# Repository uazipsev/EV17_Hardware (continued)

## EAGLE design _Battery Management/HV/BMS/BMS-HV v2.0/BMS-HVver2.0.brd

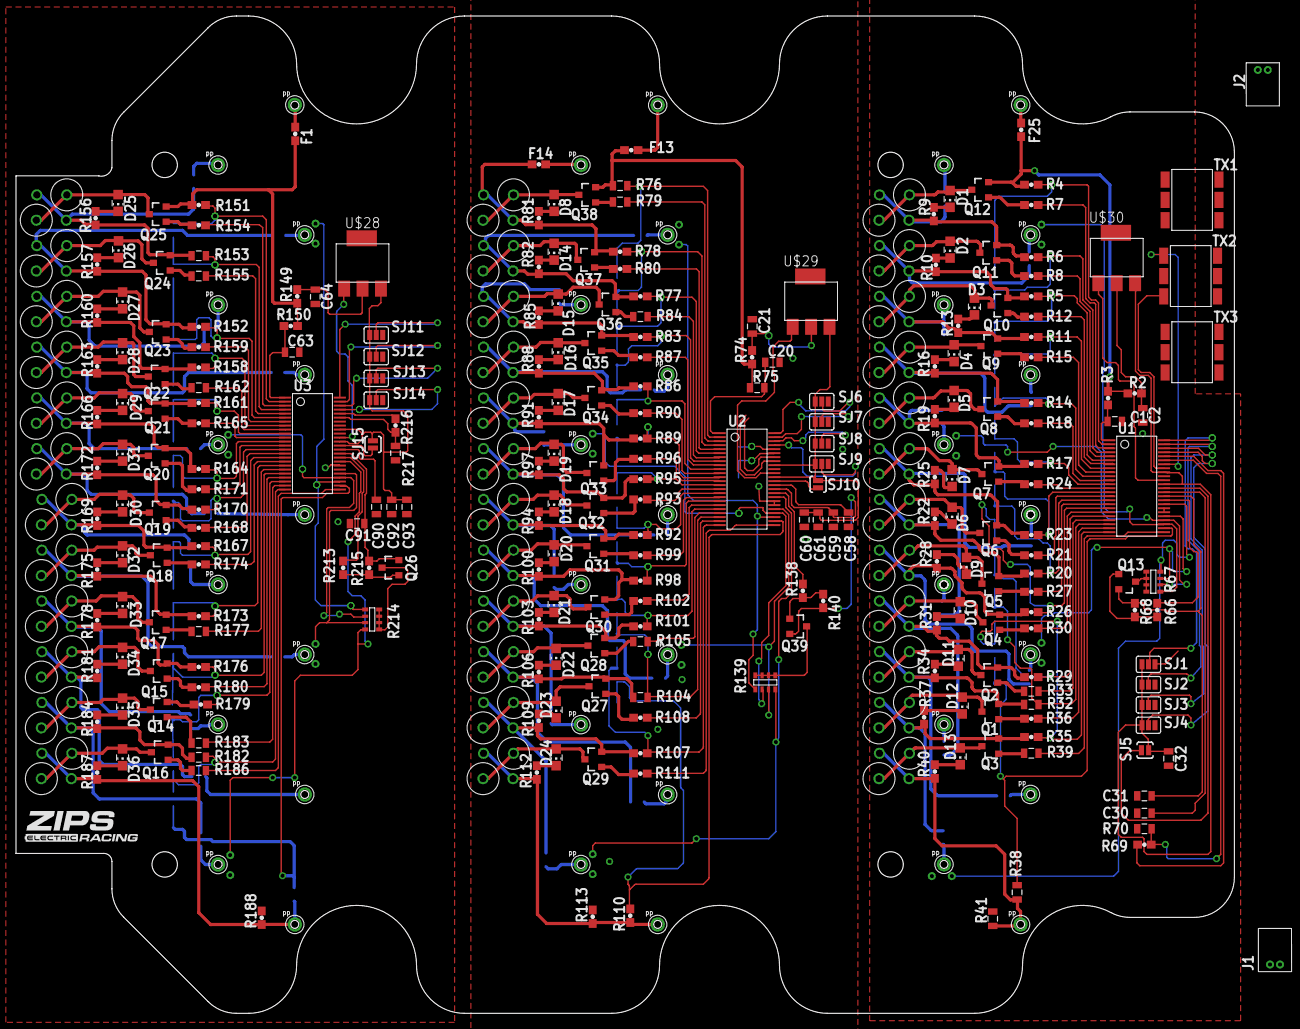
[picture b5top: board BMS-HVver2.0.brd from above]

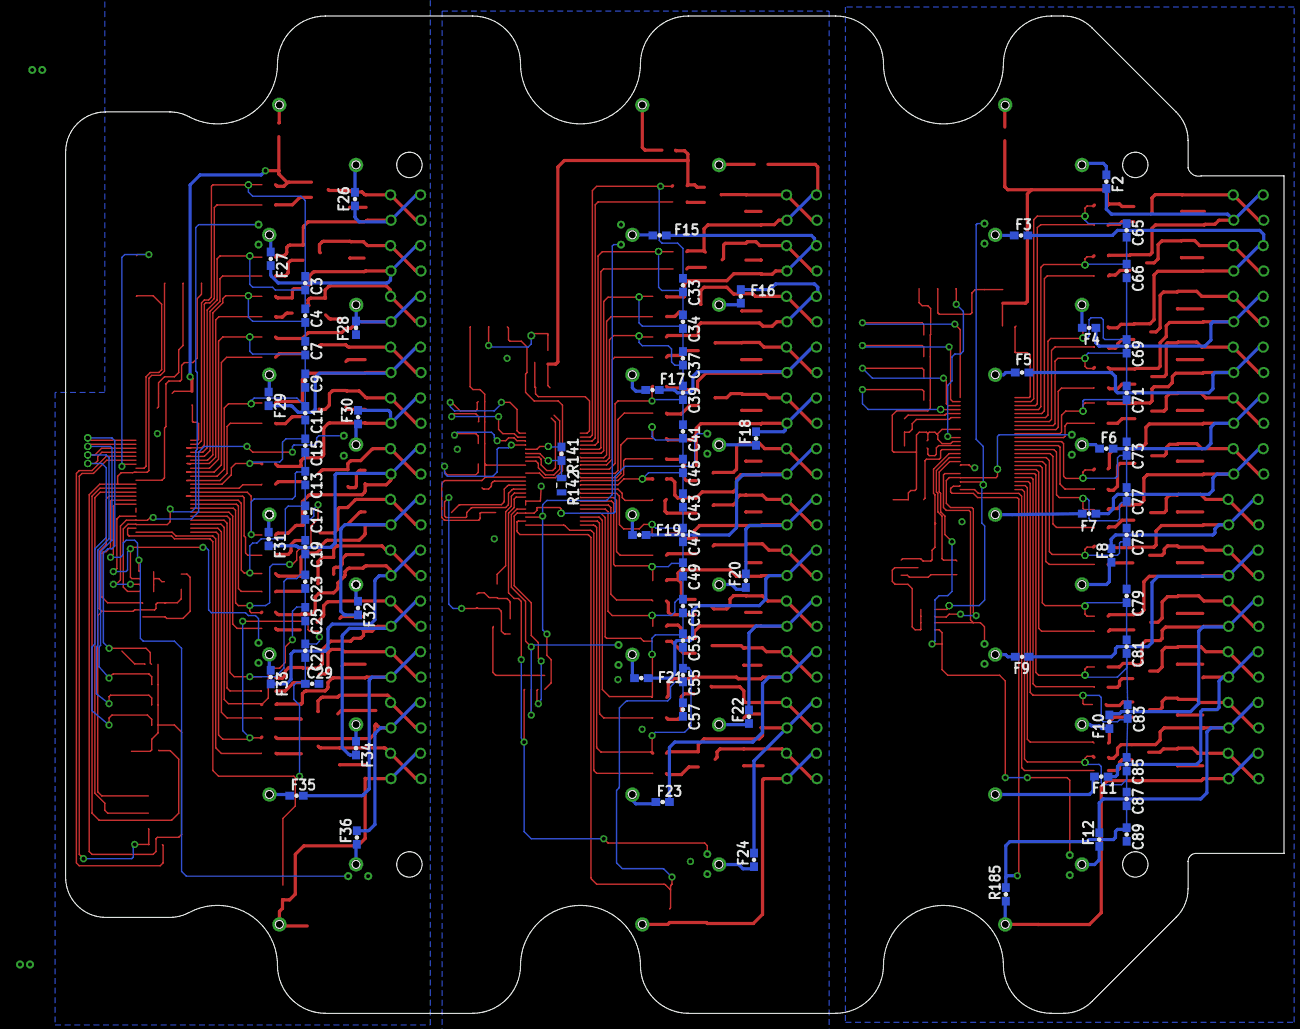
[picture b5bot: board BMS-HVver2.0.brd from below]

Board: 2 copper layers, 152.4 x 124.8 mm, 452 parts (74 on the bottom side), 329 nets.

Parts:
C1, C2, C20, C21, C63, C64: 0.1UF; 0805
C3, C4, C7, C9, C11, C13, C15, C17, C19, C23, C25, C27, C29, C33, C34, C37, C39, C41, C43, C45, C47, C49, C51, C53, C55, C57, C65, C66, C69, C71, C73, C75, C77, C79, C81, C83, C85, C87, C89: 10NF; 0603
C30, C31, C32, C58, C59, C60, C61, C90, C91, C92, C93: 1UF; 0805
D1, D2, D3, D4, D5, D6, D7, D8, D9, D10, D11, D12, D13, D14, D15, D16, D17, D18, D19, D20, D21, D22, D23, D24, D25, D26, D27, D28, D29, D30, D31, D32, D33, D34, D35, D36: LED_RED; CHIP_LED0805
F1, F2, F3, F4, F5, F6, F7, F8, F9, F10, F11, F12, F13, F14, F15, F16, F17, F18, F19, F20, F21, F22, F23, F24, F25, F26, F27, F28, F29, F30, F31, F32, F33, F34, F35, F36: FUSE_750MA_63V_0603; 0603
J1, J2: M2_DF13-2P; DF13-2P
Q1, Q2, Q3, Q4, Q5, Q6, Q7, Q8, Q9, Q10, Q11, Q12, Q13, Q14, Q15, Q16, Q17, Q18, Q19, Q20, Q21, Q22, Q23, Q24, Q25, Q26, Q27, Q28, Q29, Q30, Q31, Q32, Q33, Q34, Q35, Q36, Q37, Q38, Q39: BSS308PE; SOT23
R2, R3, R4, R5, R6, R11, R14, R17, R20, R23, R26, R29, R35, R74, R77, R78, R83, R86, R89, R92, R95, R98, R101, R107, R110, R149, R150, R151, R152, R158, R161, R164, R167, R170, R173, R176, R179, R185: 100; 0603
R7, R8, R12, R15, R18, R21, R24, R27, R30, R36, R80, R87, R90, R93, R96, R99, R102, R108, R111, R154, R159, R165, R168, R171, R174, R180: 3.3K; 0603
R9, R10, R13, R16, R19, R22, R25, R28, R31, R34, R37, R40, R81, R82, R85, R88, R91, R94, R97, R100, R103, R106, R109, R112, R156, R157, R160, R163, R166, R169, R172, R175, R178, R181, R184, R187: 475; 0603
R32, R38, R75, R76, R104, R153, R182: 100; 0805
R33, R39, R79, R84, R105, R155, R162, R177, R183, R186: 3.3K; 0805
R41: 0; 0805
R42, R43, R44, R45, R46, R47, R48, R49, R50, R51, R52, R53, R54, R55, R56, R57, R58, R59, R60, R61, R62, R63, R64, R65, R114, R115, R116, R117, R118, R119, R120, R121, R122, R123, R124, R125, R126, R127, R128, R129, R130, R131, R132, R133, R134, R135, R136, R137, R189, R190, R191, R192, R193, R194, R195, R196, R197, R198, R199, R200, R201, R202, R203, R204, R205, R206, R207, R208, R209, R210, R211, R212: 16; RR02J16RTB
R66, R138, R213: 1K; 0603
R67, R139, R214: 10K; MNR14
R68, R140, R215: 100K; 0603
R69, R141, R216: 1.2K; 0603
R70, R142, R217: 787; 0805
R71, R72, R73, R143, R144, R145, R146, R147, R218, R219, R220, R221: 10K-NTC; NTC-NXRT15XH103FA5B
R113, R188: 0; 0603
SJ1, SJ2, SJ3, SJ4, SJ6, SJ7, SJ8, SJ9, SJ11, SJ12, SJ13, SJ14: PAD-JUMPER-3-NO_YES_SILK
SJ5, SJ10, SJ15: PAD-JUMPER-2-NO_YES_SILK
TX1, TX2, TX3: PE-68386NLT
U1, U2, U3: LTC6804-2; SSOP-48
U$1, U$2, U$3, U$4, U$5, U$6, U$7, U$8, U$9, U$10, U$11, U$12, U$13, U$14, U$15, U$16, U$17, U$18, U$19, U$20, U$21, U$22, U$23, U$24, U$25, U$26, U$40, U$41, U$42, U$43, U$44, U$45, U$46, U$47, U$48, U$49, U$50, U$51, U$52: POGOPIN
U$27: LOGO16-2-L; 2016-2-LOGO-L
U$28, U$29, U$30: NSV1C201MZ4T1G; SOT223

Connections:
A0: SJ9.2, U2.45
A1: SJ8.2, U2.46
A2: SJ7.2, U2.47
A3: SJ6.2, U2.48
A4: SJ4.2, U1.45
A5: SJ3.2, U1.46
A6: SJ2.2, U1.47
A7: SJ1.2, U1.48
A8: SJ14.2, U3.45
A9: SJ13.2, U3.46
A10: SJ12.2, U3.47
A11: SJ11.2, U3.48
C0: C55.2, C57.1, R110.2, U2.26
C1: C53.2, C55.1, R107.2, U2.24
C2: C51.2, C53.1, R104.2, U2.22
C3: C49.2, C51.1, R101.2, U2.20
C4: C47.2, C49.1, R98.2, U2.18
C5: C43.2, C47.1, R92.2, U2.16
C6: C43.1, C45.2, R95.2, U2.14
C7: C41.2, C45.1, R89.2, U2.12
C8: C39.2, C41.1, R86.2, U2.10
C9: C37.2, C39.1, R83.2, U2.8
C10: C34.2, C37.1, R77.2, U2.6
C11: C33.2, C34.1, R78.2, U2.4
C12: C33.1, R76.2, U2.2
C13: C3.1, R4.2, U1.2
C14: C3.2, C4.1, R6.2, U1.4
C15: C7.2, C9.1, R11.2, U1.8
C16: C11.2, C15.1, R17.2, U1.12
C17: C13.1, C15.2, R23.2, U1.14
C18: C13.2, C17.1, R20.2, U1.16
C19: C19.2, C23.1, R29.2, U1.20
C20: C23.2, C25.1, R32.2, U1.22
C21: C25.2, C27.1, R35.2, U1.24
C22: C4.2, C7.1, R5.2, U1.6
C23: C27.2, C29.1, R38.2, U1.26
C24: C17.2, C19.1, R26.2, U1.18
C25: C9.2, C11.1, R14.2, U1.10
C26: C65.1, R151.2, U3.2
C27: C65.2, C66.1, R153.2, U3.4
C28: C69.2, C71.1, R158.2, U3.8
C29: C73.2, C77.1, R164.2, U3.12
C30: C75.1, C77.2, R170.2, U3.14
C31: C75.2, C79.1, R167.2, U3.16
C32: C81.2, C83.1, R176.2, U3.20
C33: C83.2, C85.1, R179.2, U3.22
C34: C85.2, C87.1, R182.2, U3.24
C35: C66.2, C69.1, R152.2, U3.6
C36: C87.2, C89.1, R185.2, U3.26
C37: C79.2, C81.1, R173.2, U3.18
C38: C71.2, C73.1, R161.2, U3.10
DRIVE: U2.38, U$29.P$1
DRIVE1: U1.38, U$30.P$1
DRIVE2: U3.38, U$28.P$1
GND: C63.2, C64.2, C89.2, C90.2, C91.2, C92.2, C93.2, R188.2, R217.1, R218.P$1, R219.P$1, R220.P$1, R221.P$1, SJ11.3, SJ12.3, SJ13.3, SJ14.3, U3.30, U3.31
GNDA: C20.2, C21.2, C57.2, C58.2, C59.2, C60.2, C61.2, R113.2, R142.1, R143.P$1, R144.P$1, R145.P$1, R146.P$1, SJ6.3, SJ7.3, SJ8.3, SJ9.3, U2.30, U2.31
GNDI: C1.2, C2.2, C29.2, C30.2, C31.2, C32.2, R41.2, R70.1, R71.P$1, R72.P$1, R73.P$1, R147.P$1, SJ1.3, SJ2.3, SJ3.3, SJ4.3, U1.30, U1.31
GPIO1: R139.1, R143.P$2, U2.27
GPIO2: R139.2, R144.P$2, U2.28
GPIO3: R139.3, R145.P$2, U2.29
GPIO4: R139.4, R146.P$2, U2.32
GPIO5: R138.2, U2.33
GPIO6: R67.2, R72.P$2, U1.28
GPIO7: R67.1, R71.P$2, U1.27
GPIO8: R67.4, R147.P$2, U1.32
GPIO9: R67.3, R73.P$2, U1.29
GPIO10: R66.2, U1.33
GPIO11: R214.2, R219.P$2, U3.28
GPIO12: R214.1, R218.P$2, U3.27
GPIO13: R214.4, R221.P$2, U3.32
GPIO14: R214.3, R220.P$2, U3.29
GPIO15: R213.2, U3.33
IBIAS: R141.2, U2.44
IBIAS1: R69.2, U1.44
IBIAS2: R216.2, U3.44
ICMP: R141.1, R142.2, U2.43
ICMP1: R69.1, R70.2, U1.43
ICMP2: R216.1, R217.2, U3.43
IMA: TX1.3, U2.41
IMA1: TX2.3, U1.41
IMA2: TX3.3, U3.41
IPA: TX1.1, U2.42
IPA1: TX2.1, U1.42
IPA2: TX3.1, U3.42
unnamed: Q12.1, R7.1
unnamed: D1.A, Q12.3, R64.P$2, R65.P$2
unnamed: D1.C, R9.2
unnamed: F26.2, Q11.2, R6.1, R9.1, R64.P$1, R65.P$1
unnamed: Q11.1, R8.1
unnamed: D2.A, Q11.3, R62.P$2, R63.P$2
unnamed: D2.C, R10.2
unnamed: F27.2, Q10.2, R5.1, R10.1, R62.P$1, R63.P$1
unnamed: Q10.1, R12.1
unnamed: D3.A, Q10.3, R60.P$2, R61.P$2
unnamed: D3.C, R13.2
unnamed: F28.2, Q9.2, R11.1, R13.1, R60.P$1, R61.P$1
unnamed: Q9.1, R15.1
unnamed: D4.A, Q9.3, R58.P$2, R59.P$2
unnamed: D4.C, R16.2
unnamed: F29.2, Q8.2, R14.1, R16.1, R58.P$1, R59.P$1
unnamed: Q8.1, R18.1
unnamed: D5.A, Q8.3, R56.P$2, R57.P$2
unnamed: D5.C, R19.2
unnamed: Q6.1, R21.1
unnamed: D6.A, Q6.3, R52.P$2, R53.P$2
unnamed: D6.C, R22.2
unnamed: F30.2, Q7.2, R17.1, R19.1, R56.P$1, R57.P$1
unnamed: Q7.1, R24.1
unnamed: D7.A, Q7.3, R54.P$2, R55.P$2
unnamed: D7.C, R25.2
unnamed: F31.2, Q6.2, R23.1, R25.1, R54.P$1, R55.P$1
unnamed: F32.2, Q5.2, R20.1, R22.1, R52.P$1, R53.P$1
unnamed: Q5.1, R27.1
unnamed: D9.A, Q5.3, R50.P$2, R51.P$2
unnamed: D9.C, R28.2
unnamed: F33.2, Q4.2, R26.1, R28.1, R50.P$1, R51.P$1
unnamed: Q4.1, R30.1
unnamed: D10.A, Q4.3, R48.P$2, R49.P$2
unnamed: D10.C, R31.2
unnamed: F34.2, Q2.2, R29.1, R31.1, R48.P$1, R49.P$1
unnamed: Q2.1, R33.1
unnamed: D11.A, Q2.3, R46.P$2, R47.P$2
unnamed: D11.C, R34.2
unnamed: F35.2, Q1.2, R32.1, R34.1, R46.P$1, R47.P$1
unnamed: Q1.1, R36.1
unnamed: D12.A, Q1.3, R44.P$2, R45.P$2
unnamed: D12.C, R37.2
unnamed: Q3.1, R39.1
unnamed: D13.C, R40.2
unnamed: F25.2, Q12.2, R2.1, R3.1, R4.1
unnamed: D13.A, Q3.3, R42.P$2, R43.P$2
unnamed: R38.1, R40.1, R41.1, R42.P$1, R43.P$1, U$1.1
unnamed: F36.2, Q3.2, R35.1, R37.1, R44.P$1, R45.P$1
unnamed: C2.1, R2.2, U$30.P$2
unnamed: Q13.3, R67.5, R67.6, R67.7, R67.8
unnamed: Q13.1, R66.1, R68.1
unnamed: Q25.1, R154.1
unnamed: D25.A, Q25.3, R211.P$2, R212.P$2
unnamed: D25.C, R156.2
unnamed: F2.2, Q24.2, R153.1, R156.1, R211.P$1, R212.P$1
unnamed: Q24.1, R155.1
unnamed: D26.A, Q24.3, R209.P$2, R210.P$2
unnamed: D26.C, R157.2
unnamed: F3.2, Q23.2, R152.1, R157.1, R209.P$1, R210.P$1
unnamed: Q23.1, R159.1
unnamed: D27.A, Q23.3, R207.P$2, R208.P$2
unnamed: D27.C, R160.2
unnamed: F4.2, Q22.2, R158.1, R160.1, R207.P$1, R208.P$1
unnamed: Q22.1, R162.1
unnamed: D28.A, Q22.3, R205.P$2, R206.P$2
unnamed: D28.C, R163.2
unnamed: F5.2, Q21.2, R161.1, R163.1, R205.P$1, R206.P$1
unnamed: Q21.1, R165.1
unnamed: D29.A, Q21.3, R203.P$2, R204.P$2
unnamed: D29.C, R166.2
unnamed: Q19.1, R168.1
unnamed: D30.A, Q19.3, R199.P$2, R200.P$2
unnamed: D30.C, R169.2
unnamed: F6.2, Q20.2, R164.1, R166.1, R203.P$1, R204.P$1
unnamed: Q20.1, R171.1
unnamed: D31.A, Q20.3, R201.P$2, R202.P$2
unnamed: D31.C, R172.2
unnamed: F7.2, Q19.2, R170.1, R172.1, R201.P$1, R202.P$1
unnamed: F8.2, Q18.2, R167.1, R169.1, R199.P$1, R200.P$1
unnamed: Q18.1, R174.1
unnamed: D32.A, Q18.3, R197.P$2, R198.P$2
unnamed: D32.C, R175.2
unnamed: F9.2, Q17.2, R173.1, R175.1, R197.P$1, R198.P$1
unnamed: Q17.1, R177.1
unnamed: D33.A, Q17.3, R195.P$2, R196.P$2
unnamed: D33.C, R178.2
unnamed: F10.2, Q15.2, R176.1, R178.1, R195.P$1, R196.P$1
unnamed: Q15.1, R180.1
unnamed: D34.A, Q15.3, R193.P$2, R194.P$2
unnamed: D34.C, R181.2
unnamed: F11.2, Q14.2, R179.1, R181.1, R193.P$1, R194.P$1
unnamed: Q14.1, R183.1
unnamed: D35.A, Q14.3, R191.P$2, R192.P$2
unnamed: D35.C, R184.2
unnamed: Q16.1, R186.1
unnamed: D36.C, R187.2
unnamed: F1.2, Q25.2, R149.1, R150.1, R151.1
unnamed: D36.A, Q16.3, R189.P$2, R190.P$2
unnamed: Q38.1, R79.1
unnamed: D8.A, Q38.3, R136.P$2, R137.P$2
unnamed: D8.C, R81.2
unnamed: R185.1, R187.1, R188.1, R189.P$1, R190.P$1, U$14.1
unnamed: F12.2, Q16.2, R182.1, R184.1, R191.P$1, R192.P$1
unnamed: C64.1, R149.2, U$28.P$2
unnamed: F14.2, Q37.2, R78.1, R81.1, R136.P$1, R137.P$1
unnamed: Q37.1, R80.1
unnamed: D14.A, Q37.3, R134.P$2, R135.P$2
unnamed: D14.C, R82.2
unnamed: F15.2, Q36.2, R77.1, R82.1, R134.P$1, R135.P$1
unnamed: Q26.3, R214.5, R214.6, R214.7, R214.8
unnamed: Q36.1, R84.1
unnamed: D15.A, Q36.3, R132.P$2, R133.P$2
unnamed: D15.C, R85.2
unnamed: F16.2, Q35.2, R83.1, R85.1, R132.P$1, R133.P$1
unnamed: Q26.1, R213.1, R215.1
unnamed: Q35.1, R87.1
unnamed: D16.A, Q35.3, R130.P$2, R131.P$2
unnamed: D16.C, R88.2
unnamed: F17.2, Q34.2, R86.1, R88.1, R130.P$1, R131.P$1
unnamed: J1.2, J2.1, TX1.6, TX2.6, TX3.6
unnamed: Q34.1, R90.1
unnamed: D17.A, Q34.3, R128.P$2, R129.P$2
unnamed: D17.C, R91.2
unnamed: J1.1, J2.2, TX1.4, TX2.4, TX3.4
unnamed: Q32.1, R93.1
unnamed: D18.A, Q32.3, R124.P$2, R125.P$2
unnamed: D18.C, R94.2
unnamed: C90.1, U3.35
unnamed: F18.2, Q33.2, R89.1, R91.1, R128.P$1, R129.P$1
unnamed: C30.1, U1.35
unnamed: Q33.1, R96.1
unnamed: D19.A, Q33.3, R126.P$2, R127.P$2
unnamed: D19.C, R97.2
unnamed: F19.2, Q32.2, R95.1, R97.1, R126.P$1, R127.P$1
unnamed: F20.2, Q31.2, R92.1, R94.1, R124.P$1, R125.P$1
unnamed: Q31.1, R99.1
unnamed: D20.A, Q31.3, R122.P$2, R123.P$2
unnamed: D20.C, R100.2
unnamed: F21.2, Q30.2, R98.1, R100.1, R122.P$1, R123.P$1
unnamed: Q30.1, R102.1
unnamed: D21.A, Q30.3, R120.P$2, R121.P$2
unnamed: D21.C, R103.2
unnamed: F22.2, Q28.2, R101.1, R103.1, R120.P$1, R121.P$1
unnamed: Q28.1, R105.1
unnamed: D22.A, Q28.3, R118.P$2, R119.P$2
unnamed: D22.C, R106.2
unnamed: F23.2, Q27.2, R104.1, R106.1, R118.P$1, R119.P$1
unnamed: Q27.1, R108.1
unnamed: D23.A, Q27.3, R116.P$2, R117.P$2
unnamed: D23.C, R109.2
unnamed: Q29.1, R111.1
unnamed: D24.C, R112.2
unnamed: F13.2, Q38.2, R74.1, R75.1, R76.1
unnamed: D24.A, Q29.3, R114.P$2, R115.P$2
unnamed: R110.1, R112.1, R113.1, R114.P$1, R115.P$1, U$40.1
unnamed: F24.2, Q29.2, R107.1, R109.1, R116.P$1, R117.P$1
unnamed: C21.1, R74.2, U$29.P$2
unnamed: Q39.3, R139.5, R139.6, R139.7, R139.8
unnamed: Q39.1, R138.1, R140.1
unnamed: F12.1, U$15.1
unnamed: F11.1, U$16.1
unnamed: F10.1, U$17.1
unnamed: F9.1, U$18.1
unnamed: F8.1, U$19.1
unnamed: F7.1, U$20.1
unnamed: F6.1, U$21.1
unnamed: F5.1, U$22.1
unnamed: F4.1, U$23.1
unnamed: F3.1, U$24.1
unnamed: F2.1, U$25.1
unnamed: F1.1, U$26.1
unnamed: F24.1, U$41.1
unnamed: F23.1, U$42.1
unnamed: F22.1, U$43.1
unnamed: F21.1, U$44.1
unnamed: F20.1, U$45.1
unnamed: F19.1, U$46.1
unnamed: F18.1, U$47.1
unnamed: F17.1, U$48.1
unnamed: F16.1, U$49.1
unnamed: F15.1, U$50.1
unnamed: F14.1, U$51.1
unnamed: F13.1, U$52.1
unnamed: F36.1, U$2.1
unnamed: F35.1, U$3.1
unnamed: F34.1, U$4.1
unnamed: F33.1, U$5.1
unnamed: F32.1, U$6.1
unnamed: F31.1, U$7.1
unnamed: F30.1, U$8.1
unnamed: F29.1, U$9.1
unnamed: F28.1, U$10.1
unnamed: F27.1, U$11.1
unnamed: F26.1, U$12.1
unnamed: F25.1, U$13.1
S1: R111.2, U2.25
S2: R108.2, U2.23
S3: R105.2, U2.21
S4: R102.2, U2.19
S5: R99.2, U2.17
S6: R93.2, U2.15
S7: R96.2, U2.13
S8: R90.2, U2.11
S9: R87.2, U2.9
S10: R84.2, U2.7
S11: R80.2, U2.5
S12: R79.2, U2.3
S13: R7.2, U1.3
S14: R8.2, U1.5
S15: R12.2, U1.7
S16: R15.2, U1.9
S17: R18.2, U1.11
S18: R21.2, U1.15
S19: R24.2, U1.13
S20: R27.2, U1.17
S21: R30.2, U1.19
S22: R33.2, U1.21
S23: R36.2, U1.23
S24: R39.2, U1.25
S25: R154.2, U3.3
S26: R155.2, U3.5
S27: R159.2, U3.7
S28: R162.2, U3.9
S29: R165.2, U3.11
S30: R168.2, U3.15
S31: R171.2, U3.13
S32: R174.2, U3.17
S33: R177.2, U3.19
S34: R180.2, U3.21
S35: R183.2, U3.23
S36: R186.2, U3.25
SWTEN: SJ10.1, U2.36
SWTEN1: SJ5.1, U1.36
SWTEN2: SJ15.1, U3.36
V+: C20.1, R75.2, U2.1
V+1: C1.1, R3.2, U1.1
V+2: C63.1, R150.2, U3.1
VREF1: C58.1, U2.35
VREF2: C59.1, Q39.2, R140.2, U2.34
VREF4: C31.1, Q13.2, R68.2, U1.34
VREF6: C91.1, Q26.2, R215.2, U3.34
VREG: C60.1, C61.1, SJ6.1, SJ7.1, SJ8.1, SJ9.1, SJ10.2, U2.37, U2.40, U$29.P$3
VREG1: C32.1, SJ1.1, SJ2.1, SJ3.1, SJ4.1, SJ5.2, U1.37, U1.40, U$30.P$3
VREG2: C92.1, C93.1, SJ11.1, SJ12.1, SJ13.1, SJ14.1, SJ15.2, U3.37, U3.40, U$28.P$3

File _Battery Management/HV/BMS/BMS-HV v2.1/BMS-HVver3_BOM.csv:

Qty-1,Part References,Value,Package,Mfg Part Num,Mfg Name,VID,Vendor Part Num,Description,Pkg Code,XREF
3,"SJ5, SJ10, SJ15",,PAD-JUMPER-2-NO_YES_SILK,***PART# '*' NOT FOUND***,*,*,*,*,*,*
12,"SJ1, SJ2, SJ3, SJ4, SJ6, SJ7, SJ8, SJ9, SJ11, SJ12, SJ13, SJ14",,PAD-JUMPER-3-NO_YES_SILK,***PART# '*' NOT FOUND***,*,*,*,*,*,*
36,"R1, R42, R43, R44, R45, R46, R47, R48, R49, R50, R51, R52, R53, R114, R115, R116, R117, R118, R119, R120, R121, R122, R123, R124, R125, R148, R189, R190, R191, R192, R193, R194, R195, R196, R197, R198",,R2512,***PART# '*' NOT FOUND***,*,*,*,*,*,*
2,"R113, R188",0,0603,CRCW06030000Z0EA,Vishay Dale,DK,541-0.0GCT-ND,RES SMD 0.0OHM JUMPER 1/10W 0603,0603 (1608 Metric),REF167
1,"R41",0,0805,RC0805JR-070RL,Yageo,DK,311-0.0ARCT-ND,RES SMD 0.0 OHM JUMPER 1/8W 0805,0805 (2012 Metric),REF310
6,"C1, C2, C20, C21, C63, C64",0.1UF,0805,CL21B104KCC5PNC,Samsung Electro-Mechanics America, Inc.,DK,1276-2447-1-ND,CAP CER 0.1UF 100V X7R 0805,0805 (2012 Metric),REF253
3,"R69, R141, R216",1.2K,0603,RC0603JR-071K2L,Yageo,DK,311-1.2KGRCT-ND,RES SMD 1.2K OHM 5% 1/10W 0603,0603 (1608 Metric),REF88
3,"R66, R138, R213",1K,0603,RC0603JR-071KL,Yageo,DK,311-1.0KGRCT-ND,RES SMD 1K OHM 5% 1/10W 0603,0603 (1608 Metric),REF84
12,"C5, C30, C31, C32, C58, C59, C60, C61, C90, C91, C92, C93",1UF,0805,UMK212F105ZG-T,Taiyo Yuden,DK,587-1308-1-ND,CAP CER 1UF 50V Y5V 0805,0805 (2012 Metric),REF17
3,"R54, R55, R56",1k,0603,RC0603JR-071KL,Yageo,DK,311-1.0KGRCT-ND,RES SMD 1K OHM 5% 1/10W 0603,0603 (1608 Metric),REF84
26,"R7, R8, R12, R15, R18, R21, R24, R27, R30, R36, R80, R87, R90, R93, R96, R99, R102, R108, R111, R154, R159, R165, R168, R171, R174, R180",3.3K,0603,RC0603JR-073K3L,Yageo,DK,311-3.3KGRCT-ND,RES SMD 3.3K OHM 5% 1/10W 0603,0603 (1608 Metric),REF89
10,"R33, R39, R79, R84, R105, R155, R162, R177, R183, R186",3.3K,0805,RC0805FR-073K3L,Yageo,DK,311-3.30KCRCT-ND,RES SMD 3.3K OHM 1% 1/8W 0805,0805 (2012 Metric),REF128
3,"R67, R139, R214",10K,MNR14,MNR14ERAPJ103,Rohm Semiconductor,DK,RHM1596CT-ND,RES ARRAY 4 RES 10K OHM 1206,1206 (3216 Metric), Convex, Long Side Terminals,REF29
39,"C3, C4, C7, C9, C11, C13, C15, C17, C19, C23, C25, C27, C29, C33, C34, C37, C39, C41, C43, C45, C47, C49, C51, C53, C55, C57, C65, C66, C69, C71, C73, C75, C77, C79, C81, C83, C85, C87, C89",10NF,0603,CL10B103KC8NNNC,Samsung Electro-Mechanics America, Inc.,DK,1276-1196-1-ND,CAP CER 10000PF 100V X7R 0603,0603 (1608 Metric),REF160
38,"R2, R3, R4, R5, R6, R11, R14, R17, R20, R23, R26, R29, R35, R74, R77, R78, R83, R86, R89, R92, R95, R98, R101, R107, R110, R149, R150, R151, R152, R158, R161, R164, R167, R170, R173, R176, R179, R185",100,0603,RC0603FR-07100RL,Yageo,DK,311-100HRCT-ND,RES SMD 100 OHM 1% 1/10W 0603,0603 (1608 Metric),REF159
7,"R32, R38, R75, R76, R104, R153, R182",100,0805,RC0805FR-07100RL,Yageo,DK,311-100CRCT-ND,RES SMD 100 OHM 1% 1/8W 0805,0805 (2012 Metric),REF307
3,"R68, R140, R215",100K,0603,RC0603JR-07100KL,Yageo,DK,311-100KGRCT-ND,RES SMD 100K OHM 5% 1/10W 0603,0603 (1608 Metric),REF90
12,"NTC1, NTC2, NTC3, NTC4, NTC5, NTC6, NTC7, NTC8, NTC9, NTC10, NTC11, NTC12",103JT-025,103JT-025,***PART# '*' NOT FOUND***,*,*,*,*,*,*
36,"R9, R10, R13, R16, R19, R22, R25, R28, R31, R34, R37, R40, R81, R82, R85, R88, R91, R94, R97, R100, R103, R106, R109, R112, R156, R157, R160, R163, R166, R169, R172, R175, R178, R181, R184, R187",475,0603,CRCW0201475RFKED,Vishay Dale,DK,541-475AABCT-ND,RES SMD 475 OHM 1% 1/20W 0201,0201 (0603 Metric),REF292
3,"R70, R142, R217",787,0805,RC0805FR-07787RL,Yageo,DK,311-787CRCT-ND,RES SMD 787 OHM 1% 1/8W 0805,0805 (2012 Metric),REF183
39,"Q1, Q2, Q3, Q4, Q5, Q6, Q7, Q8, Q9, Q10, Q11, Q12, Q13, Q14, Q15, Q16, Q17, Q18, Q19, Q20, Q21, Q22, Q23, Q24, Q25, Q26, Q27, Q28, Q29, Q30, Q31, Q32, Q33, Q34, Q35, Q36, Q37, Q38, Q39",BSS308PE,SOT23,BSS308PE H6327,Infineon Technologies,DK,BSS308PE H6327CT-ND,MOSFET P-CH 30V 2A SOT23,SOT-23-3,REF291
36,"F1, F2, F3, F4, F5, F6, F7, F8, F9, F10, F11, F12, F13, F14, F15, F16, F17, F18, F19, F20, F21, F22, F23, F24, F25, F26, F27, F28, F29, F30, F31, F32, F33, F34, F35, F36",FUSE_750MA_63V_0603,0603,C2Q 750,Bel Fuse Inc.,DK,507-1090-1-ND,FUSE BOARD MNT 750MA 32VAC 63VDC,0603 (1608 Metric),REF309
3,"D37, D38, D39",LED_AMBER,CHIP_LED0805,HSMA-C170,Avago Technologies US Inc.,DK,516-1431-1-ND,LED AMBER DIFFUSED 0805 SMD,0805 (2012 Metric),REF39
36,"D1, D2, D3, D4, D5, D6, D7, D8, D9, D10, D11, D12, D13, D14, D15, D16, D17, D18, D19, D20, D21, D22, D23, D24, D25, D26, D27, D28, D29, D30, D31, D32, D33, D34, D35, D36",LED_RED,CHIP_LED0805,LH R974-LP-1,OSRAM Opto Semiconductors Inc.,DK,475-1415-1-ND,LED RED DIFFUSED 0805 SMD,0805 (2012 Metric),REF36
1,"U$27",LOGO16-2-L,2016-2-LOGO-L,***PART# '*' NOT FOUND***,*,*,*,*,*,*
3,"U1, U2, U3",LTC6804-2,SSOP-48,LTC6804IG-2#PBF,Linear Technology,DK,LTC6804IG-2#PBF-ND,IC MONITOR BATT STACK 48SSOP,48-FSOP (0.209", 5.30mm Width),REF215
2,"J3, J4",M2S02B-PASK-2(LF)(SN),S02B-PASK-2(LF)(SN),***PART# 'S02B-PASK-2(LF)(SN)' NOT FOUND***,*,*,*,*,*,*
3,"U$28, U$29, U$30",NSV1C201MZ4T1G,SOT223,***PART# 'NSV1C201MZ4T1G' NOT FOUND***,*,*,*,*,*,*
3,"TX1, TX2, TX3",PE-68386NLT,PE-68386NLT,PE-68386NLT,Pulse Electronics Corporation,DK,553-1776-1-ND,XFRMR GATE DRIVE 1:1 785UH SMD,None,REF166
39,"U$1, U$2, U$3, U$4, U$5, U$6, U$7, U$8, U$9, U$10, U$11, U$12, U$13, U$14, U$15, U$16, U$17, U$18, U$19, U$20, U$21, U$22, U$23, U$24, U$25, U$26, U$40, U$41, U$42, U$43, U$44, U$45, U$46, U$47, U$48, U$49, U$50, U$51, U$52",POGOPIN,POGOPIN,***PART# '*' NOT FOUND***,*,*,*,*,*,*
